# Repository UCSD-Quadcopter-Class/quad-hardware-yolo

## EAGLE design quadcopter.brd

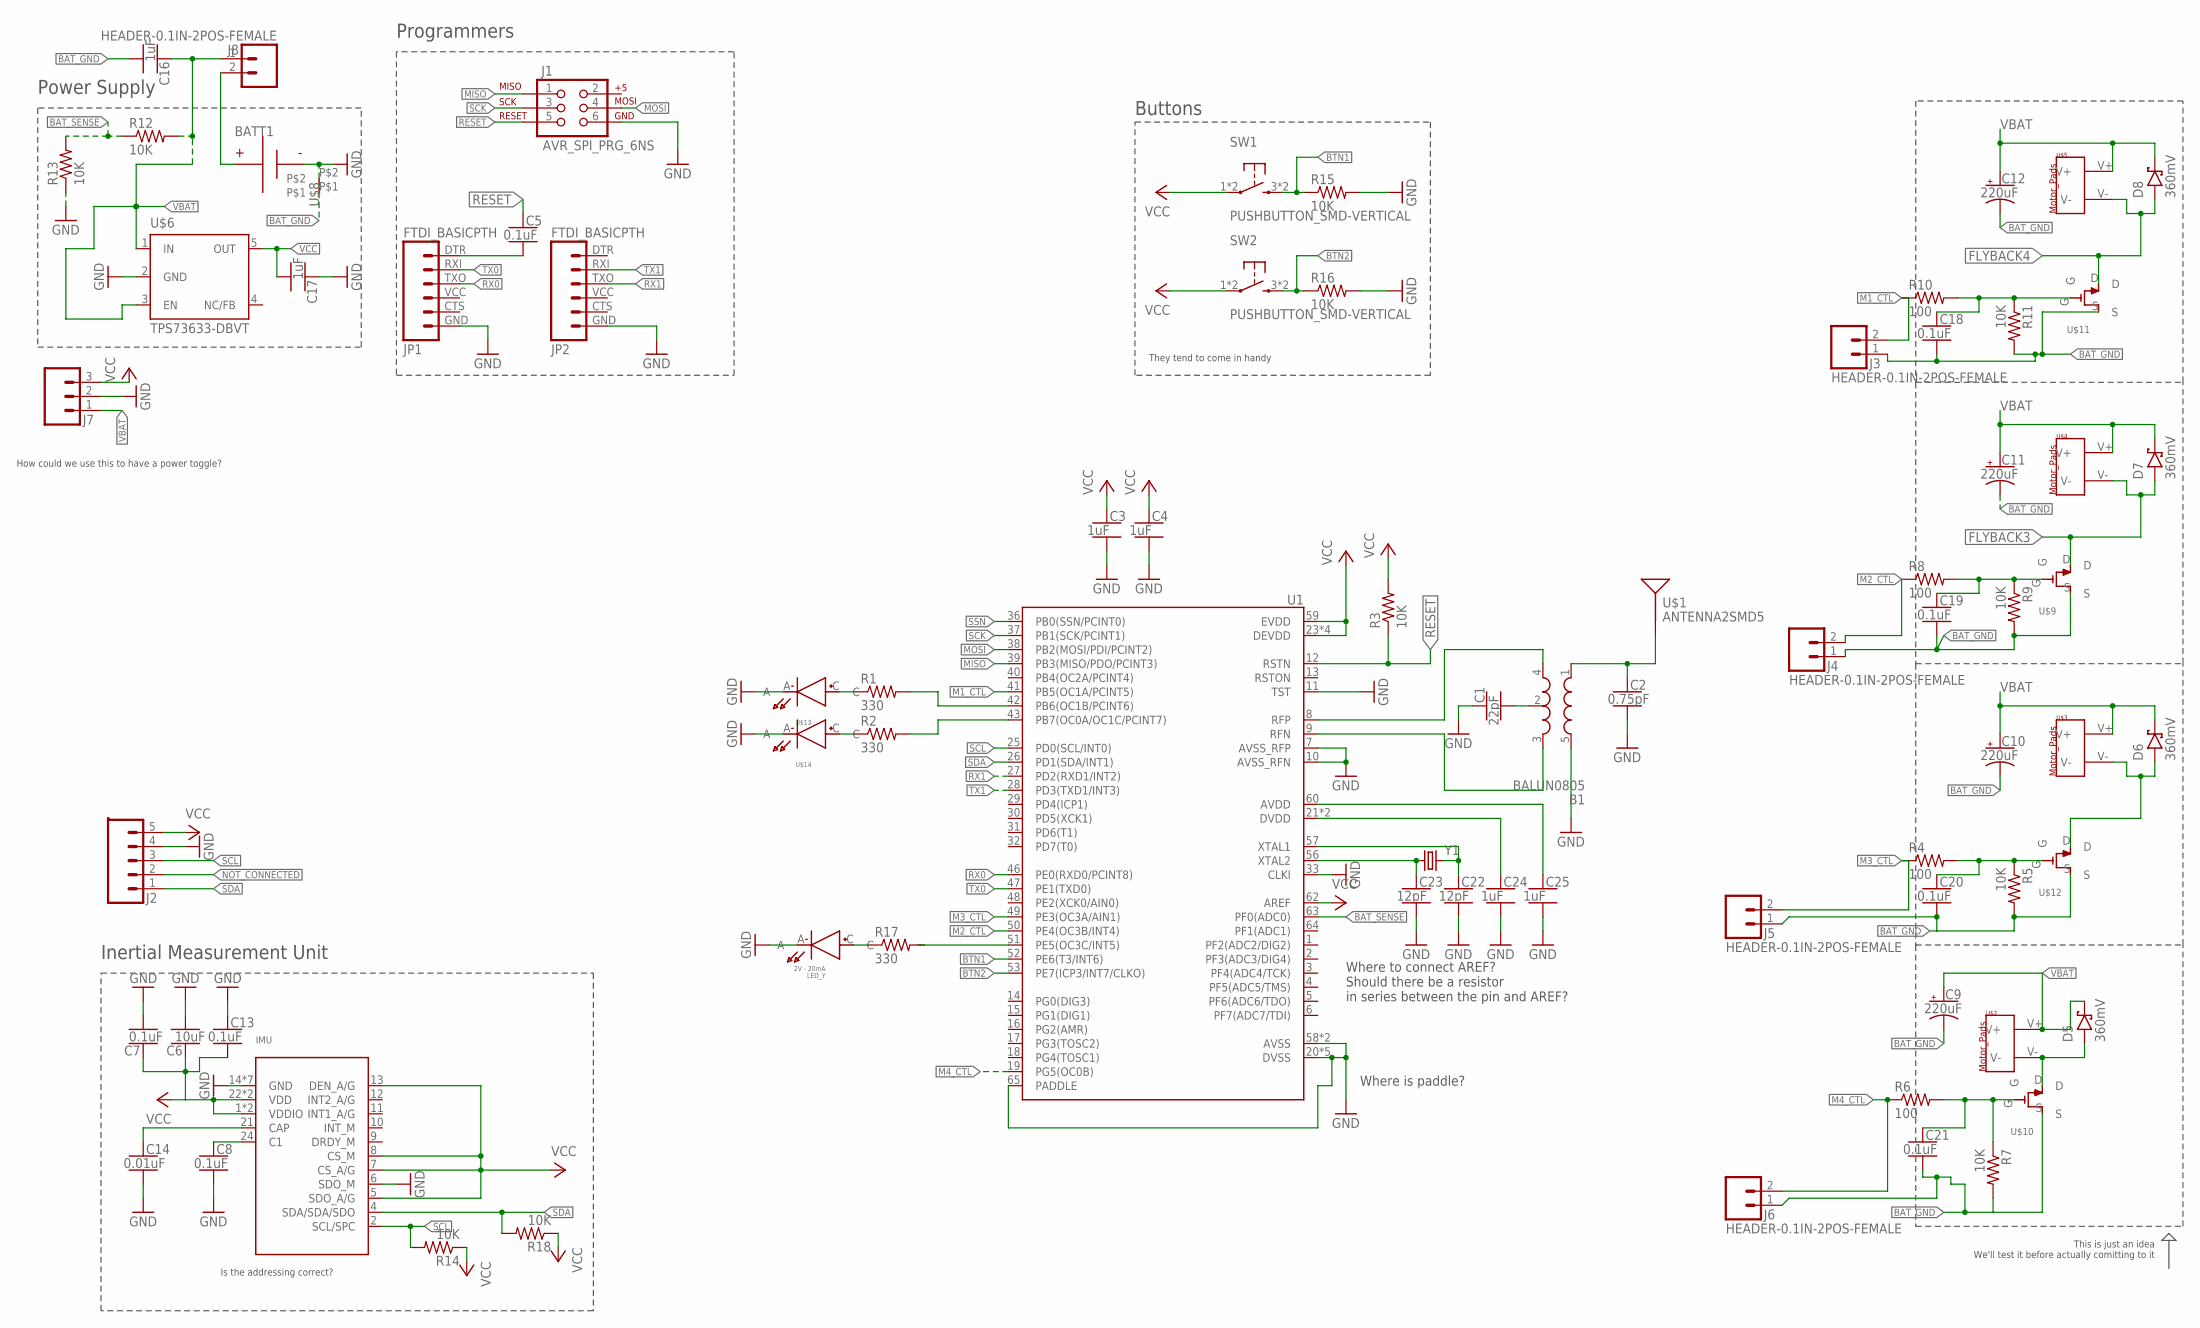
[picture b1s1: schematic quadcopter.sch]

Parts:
B1: BALUN0805; BALUN
BATT1: BATTERY-HUBSAN-W/HOLDER; BATTERY-W/HOLDER-380MAH-HUBSAN
C1: 22pF; CAPC2012X140_HS
C2: 0.75pF; CAPC2012X140_HS
C3, C4, C16, C17, C24, C25: 1uF; CAPC2012X140_HS
C5, C7, C8, C13, C18, C19, C20, C21: 0.1uF; CAPC2012X140_HS
C6: 10uF; CAPC2012X140_HS
C9, C10, C11, C12: 220uF; CAPMP7343X310_HS
C14: 0.01uF; CAPC2012X140_HS
C22, C23: 12pF; CAPC2012X140_HS
D5, D6, D7, D8: 360mV; SOD3716X135_HS
IMU: IMU; IMU_LSM9DS1TR
J1: AVR_SPI_PRG_6NS; 2X3-NS
J2: HEADER-0.1IN-5POS-FEMALE; HDRV5W63P254_5X1_1270X254H838_HS
J3, J4, J5, J6, J8: HEADER-0.1IN-2POS-FEMALE; HDRV2W63P254_2X1_508X254H838_HS
J7: HEADER-0.1IN-3POS-MALE; HDRV3W63P254_3X1_762X254H838_HS
JP1, JP2: FTDI_BASICPTH; FTDI_BASIC
LED_Y: 2V - 20mA; LED_LTST-C170EKT
R1, R2, R17: 330; RESC2012X60_HS
R3, R5, R7, R9, R11, R12, R13, R14, R15, R16, R18: 10K; RESC2012X60_HS
R4, R6, R8, R10: 100; RESC2012X60_HS
SW1, SW2: PUSHBUTTON_SMD-VERTICAL; TE_FSM8JSMA_HS
U1: ATMEGA128RFA1; QFN-64
U$1: ANTENNA2SMD5; ANTENNA-CHIP5
U$2, U$3, U$4, U$5: MOTOR_PADS
U$6: TPS73633-DBVT; SOT23-DBV
U$8: NET_BRIDGE
U$9, U$10, U$11, U$12: N-FET; N_FET_SI2302CDS-T1-E3CT-ND
U$13, U$14: LED-RED; LED_LTST-C170EKT
Y1: CRYSTAL5X3; CRYSTAL-SMD-5X3

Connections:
ATTENNA: B1.1 (IN), C2.1, U$1.FEED
BAT_GND: C9.2 (-), C10.2 (-), C11.2 (-), C12.2 (-), C16.2, C18.2, C19.2, C20.2, C21.2, J3.1, J4.1, J5.1, J6.1, R5.2, R7.2, R9.2, R11.2, U$8.P$1, U$9.S, U$10.S, U$11.S, U$12.S
BAT_SENSE: R12.1, R13.2, U1.63 (PF0(ADC0))
BTN1: R15.1, SW1.3 (2), SW1.4 (2), U1.52 (PE6(T3/INT6))
BTN2: R16.1, SW2.3 (2), SW2.4 (2), U1.53 (PE7(ICP3/INT7/CLKO))
FLYBACK2: D6.A, U$3.V-, U$12.D
FLYBACK3: D7.A, U$4.V-, U$9.D
FLYBACK4: D8.A, U$5.V-, U$11.D
GND: B1.5 (GND), BATT1.- (N), C1.1, C2.2, C3.2, C4.2, C6.2, C7.2, C8.2, C13.1, C14.2, C17.1, C22.2, C23.2, C24.2, C25.2, IMU.6 (SDO_M), IMU.14 (GND), IMU.15 (GND), IMU.16 (GND), IMU.17 (GND), IMU.18 (GND), IMU.19 (GND), IMU.20 (GND), J1.6, J2.4, J7.2, JP1.GND (6), JP2.GND (6), LED_Y.A, R13.1, R15.2, R16.2, U1.7 (AVSS_RFP), U1.10 (AVSS_RFN), U1.11 (TST), U1.20 (DVSS), U1.24 (DVSS), U1.33 (CLKI), U1.35 (DVSS), U1.45 (DVSS), U1.55 (DVSS), U1.58 (AVSS), U1.61 (AVSS), U1.65 (PADDLE), U$6.2 (GND), U$8.P$2, U$13.A, U$14.A
M1_CTL: J3.2, R10.1, U1.41 (PB5(OC1A/PCINT5))
M2_CTL: J4.2, R8.1, U1.50 (PE4(OC3B/INT4))
M3_CTL: J5.2, R4.1, U1.49 (PE3(OC3A/AIN1))
M4_CTL: J6.2, R6.1, U1.19 (PG5(OC0B))
MISO: J1.1, U1.39 (PB3(MISO/PDO/PCINT3))
MOSI: J1.4, U1.38 (PB2(MOSI/PDI/PCINT2))
unnamed: C5.2, JP1.DTR (1)
unnamed: R2.2, U1.43 (PB7(OC0A/OC1C/PCINT7))
unnamed: B1.2 (GND), C1.2
unnamed: R1.2, U1.42 (PB6(OC1B/PCINT6))
unnamed: R1.1, U$13.C
unnamed: R2.1, U$14.C
unnamed: D5.A, U$2.V-, U$10.D
unnamed: C20.1, R4.2, R5.1, U$12.G
unnamed: C8.1, IMU.24 (C1)
unnamed: BATT1.+, J8.2
unnamed: C19.1, R8.2, R9.1, U$9.G
unnamed: C21.1, R6.2, R7.1, U$10.G
unnamed: C18.1, R10.2, R11.1, U$11.G
unnamed: C14.1, IMU.21 (CAP)
unnamed: C22.1, U1.57 (XTAL1), Y1.3 (2)
unnamed: R17.2, U1.51 (PE5(OC3C/INT5))
unnamed: LED_Y.C, R17.1
unnamed: C23.1, U1.56 (XTAL2), Y1.1
unnamed: C24.1, U1.21 (DVDD), U1.22 (DVDD)
unnamed: C25.1, U1.60 (AVDD)
NOT_CONNECTED: J2.2
RESET: C5.1, J1.5, R3.1, U1.12 (RSTN)
RFN: B1.3 (OUT2), U1.9 (RFN)
RFP: B1.4 (OUT1), U1.8 (RFP)
RX0: JP1.TXO (3), U1.46 (PE0(RXD0/PCINT8))
RX1: JP2.TXO (3), U1.27 (PD2(RXD1/INT2))
SCK: J1.3, U1.37 (PB1(SCK/PCINT1))
SCL: IMU.2 (SCL/SPC), J2.3, R14.2, U1.25 (PD0(SCL/INT0))
SDA: IMU.4 (SDA/SDA/SDO), J2.1, R18.2, U1.26 (PD1(SDA/INT1))
SSN: U1.36 (PB0(SSN/PCINT0))
TX0: JP1.RXI (2), U1.47 (PE1(TXD0))
TX1: JP2.RXI (2), U1.28 (PD3(TXD1/INT3))
VBAT: C9.1 (+), C10.1 (+), C11.1 (+), C12.1 (+), C16.1, D5.C, D6.C, D7.C, D8.C, J7.1, J8.1, R12.2, U$2.V+, U$3.V+, U$4.V+, U$5.V+, U$6.1 (IN), U$6.3 (EN)
VCC: C3.1, C4.1, C6.1, C7.1, C13.2, C17.2, IMU.1 (VDDIO), IMU.3 (VDDIO), IMU.5 (SDO_A/G), IMU.7 (CS_A/G), IMU.8 (CS_M), IMU.13 (DEN_A/G), IMU.22 (VDD), IMU.23 (VDD), J2.5, J7.3, R3.2, R14.1, R18.1, SW1.1, SW1.2 (1), SW2.1, SW2.2 (1), U1.23 (DEVDD), U1.34 (DEVDD), U1.44 (DEVDD), U1.54 (DEVDD), U1.59 (EVDD), U1.62 (AREF), U$6.5 (OUT)

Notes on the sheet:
Where is paddle?
Where to connect AREF? Should there be a resistor in series between the pin and AREF?
Power Supply
Programmers
Inertial Measurement Unit
This is just an idea We'll test it before actually comitting to it
Buttons
They tend to come in handy
Is the addressing correct?
How could we use this to have a power toggle?

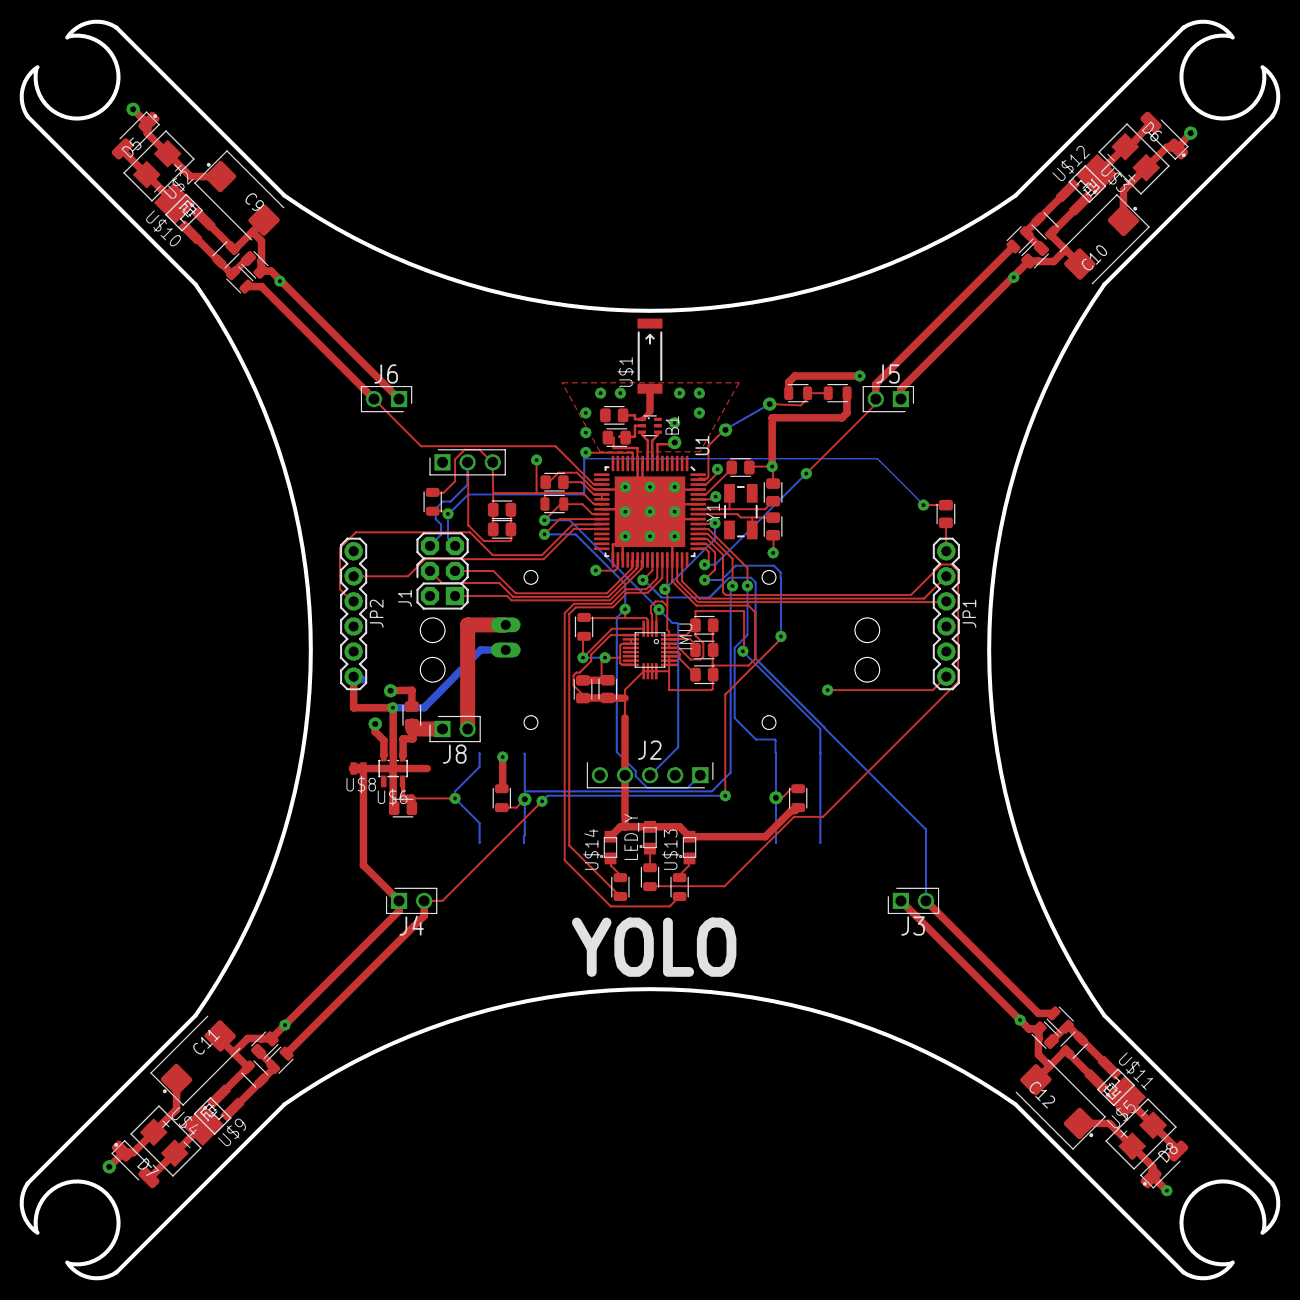
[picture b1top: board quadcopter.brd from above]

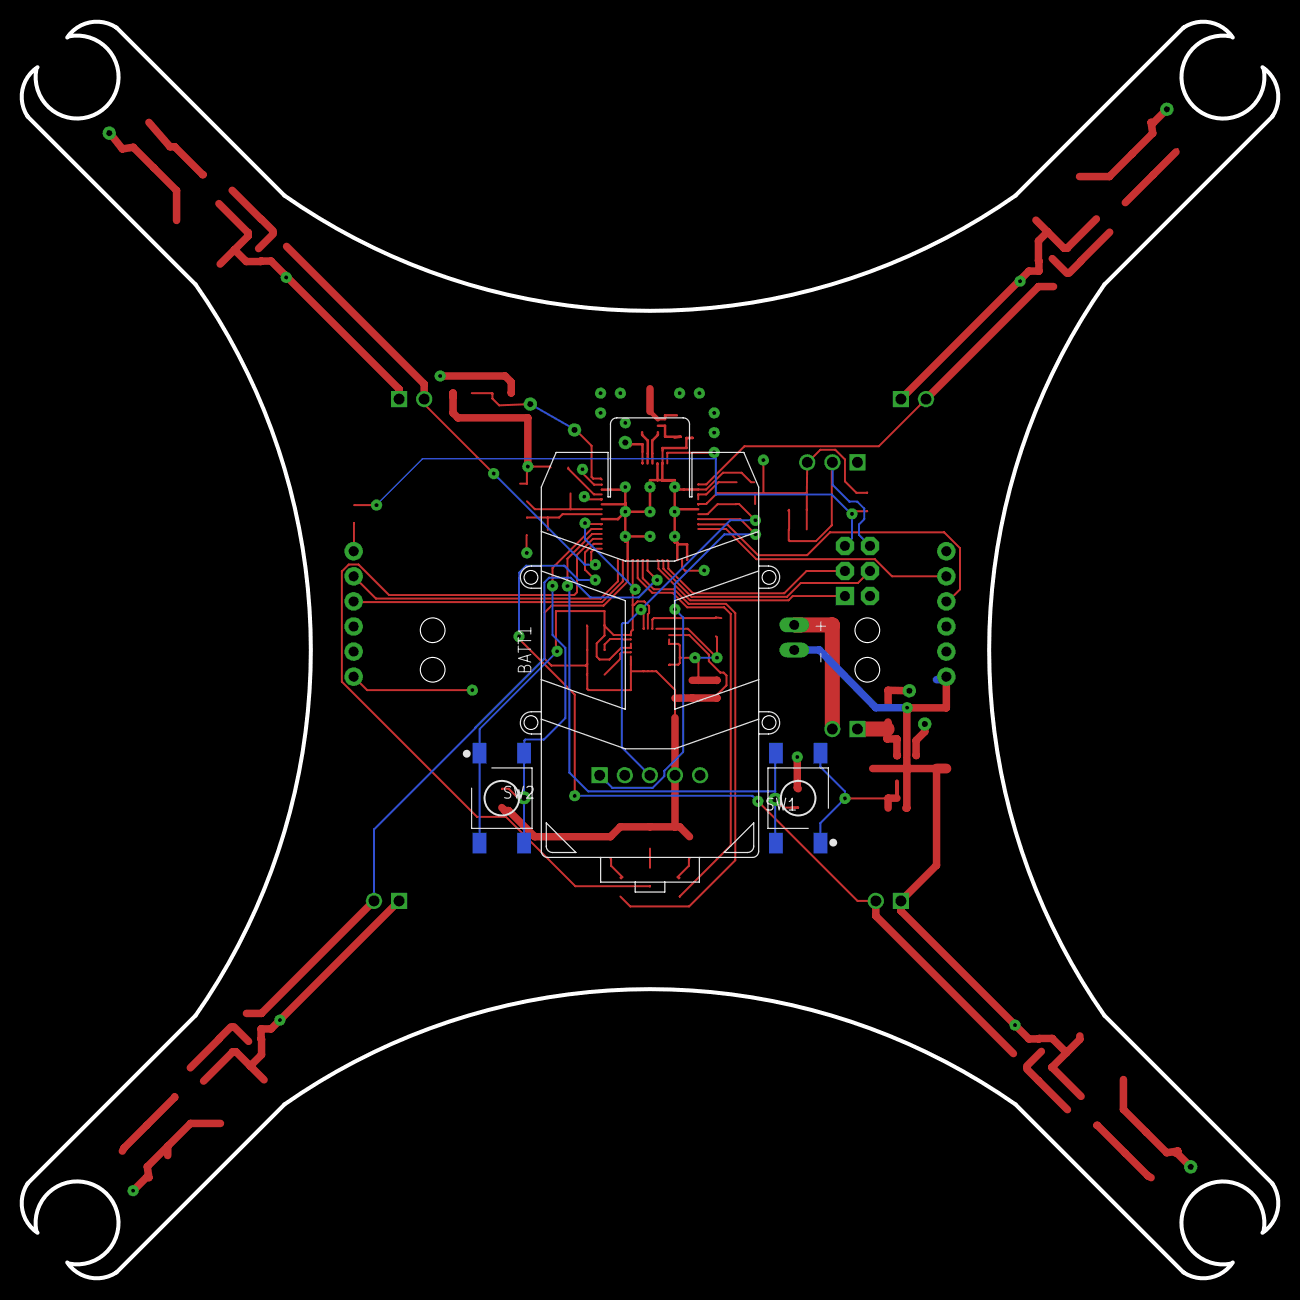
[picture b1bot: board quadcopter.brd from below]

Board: 4 copper layers, 127.2 x 127.2 mm, 77 parts (3 on the bottom side), 47 nets.

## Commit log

2017-04-18 added my lab2 lib
2017-04-18 Starting schematic
2017-04-18 Added motors
2017-04-18 Added voltage regulator and imu
2017-04-18 adding gitignore
2017-04-18 mostly finished
2017-04-20 Many updates
2017-04-20 Fixed IMU pin mappings
2017-04-20 Using LEDs from previous lab
2017-04-20 passing eagle lint
2017-04-20 added txt files
2017-04-20 cleaning directories
2017-04-24 updated motor schematic
2017-04-24 removed gadgetron grounds
2017-04-24 added questions
2017-04-25 Fixed spacing issue and reset issue
2017-04-25 started board
2017-04-25 added bmp280 as submodule
2017-04-26 started laying out basic board
2017-04-26 basic board layout added
2017-04-26 made board more curvy
2017-04-26 board updates
2017-04-26 fancy layout
2017-04-27 instructior review of original schematic
2017-04-28 made motor drivers all neat, tried to organize rest of components more neatly as well
2017-05-01 laid components more nicely
2017-05-01 Did some really careful math for placing prop grips
2017-05-01 Fixed n-fet and imu packages
2017-05-01 routed radio
2017-05-01 added i2c pullups, placed oscillator components
2017-05-01 layed down bat plane
2017-05-01 Layed out power planes
2017-05-02 found a much better way to layout pours
2017-05-02 further isolated attenna
2017-05-02 preautoroute
2017-05-02 swaped motor 2 and 4
2017-05-02 passing parts of drc
2017-05-02 Made tkeepouts stricter on imu, laid out components out nicer
2017-05-02 autorouted
2017-05-04 Added board reviews
2017-05-04 initial cam, has 2 missing soldermask clearance violations, one for netbridge which is ok, and other for vias that consist of the faraday cage
2017-05-08 Made cutout in pour for imu
2017-05-08 fixed pwm filters
2017-05-08 Manually routed motors
2017-05-08 More manual routing
2017-05-08 too much manual routing
2017-05-11 manually routed a lot of traces from the microcontroller and imu to make autorouter run significantly better, also symetrically laid out the motors and motor pins. cam files appear to have passed fre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
2017-05-11 updated some of the traces to make them nicer, also rerouted autorouted trace that went under imu
2017-05-11 final touches on internal routes, everything still passes cam, looks ready for review
2017-05-11 added documentation on netbridge DFM potential show stopper
2017-05-11 most up to date cam files
2017-05-11 Approving stopmask bugs
2017-05-11 approved more restrict errors for antenna components
2017-05-11 moved bottom trace out of restrict area for IMU
2017-05-11 spaced vias to right of microcontroller further apart, also noticed vias in faraday cage are close together
2017-05-11 moved and resized a few vias
2017-05-11 generated new cam file
2017-05-11 fixed small hole near net bridge
2017-05-11 updated cam
2017-05-11 MY review
2017-05-12 positioned crystal better, need to reroute a couple traces
2017-05-12 oscillator complete, traces rerouted and added more ground vias to reduce surface grounds
2017-05-12 more ground connections
2017-05-12 updated imu package to make pads smaller, no more clearance issues with that now
2017-05-12 started to fix attenna pours
2017-05-12 updated imu on board, rerouted some dangerous looking wires, approved drc
2017-05-12 minor updates
2017-05-14 fixed attenna
2017-05-14 changed caps, moving grounds
2017-05-15 remapped and rewired M2_CTL and M3_CTL since the pins they were on were not originally PWM pins
2017-05-15 dunno what i just did
2017-05-15 fixed diode pads
2017-05-15 added updated flybacks to board
2017-05-15 renaming parts
2017-05-15 updated cam files
2017-05-15 made farady cage tighter, added heat sink
2017-05-15 merge
2017-05-15 More gnd cleaning
2017-05-15 fixed loop near netbridge, added yolo to board, moved caps
